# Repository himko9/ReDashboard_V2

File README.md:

# N-in-One Enhanced ReDashboard - Open-Source "EZ Dashboard" Based on the RP2040 MCU

English | [简体中文](./README.zh-CN.md)

<table>
  <tr>
    <td></td>
    <td></td>
  </tr>
  <tr>
    <td></td>
    <td></td>
  </tr>
</table>

### Motherboard Support:

**Supports POST code monitoring through the following headers/interfaces:**

* JDASH1

* JDP1

* JBD1

* Any other UART header using 115200-8N1

**On MSI motherboards, connecting to "JDASH1" provides:**

* Display and logging of POST codes (Port80/81, 8-bit)

* Fan speed display

* System temperature display

* System voltage display

**On MSI motherboards, connecting to "JDP1" provides:**

* Display and logging of POST codes (Port80, 32-bit; Port81-83, 8-bit)

**On other motherboards, connecting to any header that outputs codes over UART 115200-8N1 provides:**

* Display and logging of POST codes (Port80, 8-bit)

**On all motherboards, additional connections to JBAT and JFP1 allow control of:**

* BIOS reset and system power on/off

### Firmware Features:

Code history:\
Supports caching P80 codes in the chip's internal memory.\
The onboard buttons can be used to scroll up and down through the recorded codes.

Code output:\
When connected via USB-C, the device operates as a USB CDC UART device.\
Supports decoded P80 code output.\
A future SDK will support voltage, temperature, and fan-speed logging.

Temperature / voltage / fan-speed sensors:\
Supports custom labels based on motherboard model.\
Supports Celsius / Fahrenheit temperature conversion.

OLED page control:\
Supports disabling unused pages, such as hiding the voltage page.\
Supports automatically returning to the home page after N seconds.\
Supports automatically waking the display when a significant change in temperature, voltage, or fan speed is detected.\
Supports automatically displaying updated POST codes.

OLED burn-in protection features:\
Pixel shifting.\
Automatic dimming.\
Automatic page-title hiding.\
Automatic display shutoff.

### Button Controls:

Short-press both side buttons -> Switch input source (JDASH/UART).\
Hold both side buttons for 3 seconds -> Switch button mode (page navigation mode / power-button mode).\
Hold both side buttons for 5 seconds -> Lock the JDASH/UART input and lock the buttons\
(buttons have no function while locked, Hold again to unlock).\
Hold both side buttons for 10 seconds -> Reset BIOS (NMOS connects JBAT1).

Press either side button 5 times consecutively -> Change page (switch display page).\
On the P80 page, hold either side button -> Scroll up/down through the P80 code history.

### BOM + Manufacturing Notes:
**If you want to reproduce the design directly, please note that the design was imported into JLCPCB/LCEDA from an external source.**\
**I cannot confirm whether Gerber files exported from this project can be used directly for PCB manufacturing.**\
**Please verify the schematic, PCB routing, and copper pours yourself.**\
**Using the Autodesk Eagle design files to generate gerber should be fine**

The reproduction cost is only about RMB 15:\
RMB 6 for a 0.96-inch, 4-pin I2C OLED module.\
RMB 5 for an RP2040 module, from which the RP2040, crystal oscillator, and SPI NOR flash are removed.\
RMB 4 for other capacitors, resistors, LDOs, and miscellaneous components.\
RMB 0 for a free 2-layer PCB (thanks to JLCPCB).

**Note:**\
Reproducing the RP2040 version of ReDashboard is not recommended here.\
A later version will use a PY32 as the main controller, reducing the chip cost significantly to about RMB 0.5, and requiring almost no external components.\
The firmware has already been written and successfully tested. It will be updated when I'm free.\
<br>

### Firmware and Firmware Source Code:
You can use the precompiled `firmware.uf2` file, but it is recommended that you modify the configuration and compile the firmware yourself.
<br>

### License:
Both the hardware and firmware of this project are licensed under the GPL (v3 or later).\
I provide no guarantees regarding the functionality or safety of this project.\
You are free to use, sell, and create products based on this project.

```
/*
 * This file is part of the "ReDashboard_V2" distribution.
 *
 * Copyright (C) 2026 @himko9 <me@himko.dev>
 * Github: https://github.com/himko9/ReDashboard_V2
 *
 * This program is free software: you can redistribute it and/or modify
 * it under the terms of the GNU General Public License as published by
 * the Free Software Foundation, either version 3 of the License, or
 * (at your option) any later version.
 *
 * This program is distributed in the hope that it will be useful,
 * but WITHOUT ANY WARRANTY; without even the implied warranty of
 * MERCHANTABILITY or FITNESS FOR A PARTICULAR PURPOSE.  See the
 * GNU General Public License for more details.
 *
 * You should have received a copy of the GNU General Public License
 * along with this program.  If not, see <https://www.gnu.org/licenses/>.
 */
 ```

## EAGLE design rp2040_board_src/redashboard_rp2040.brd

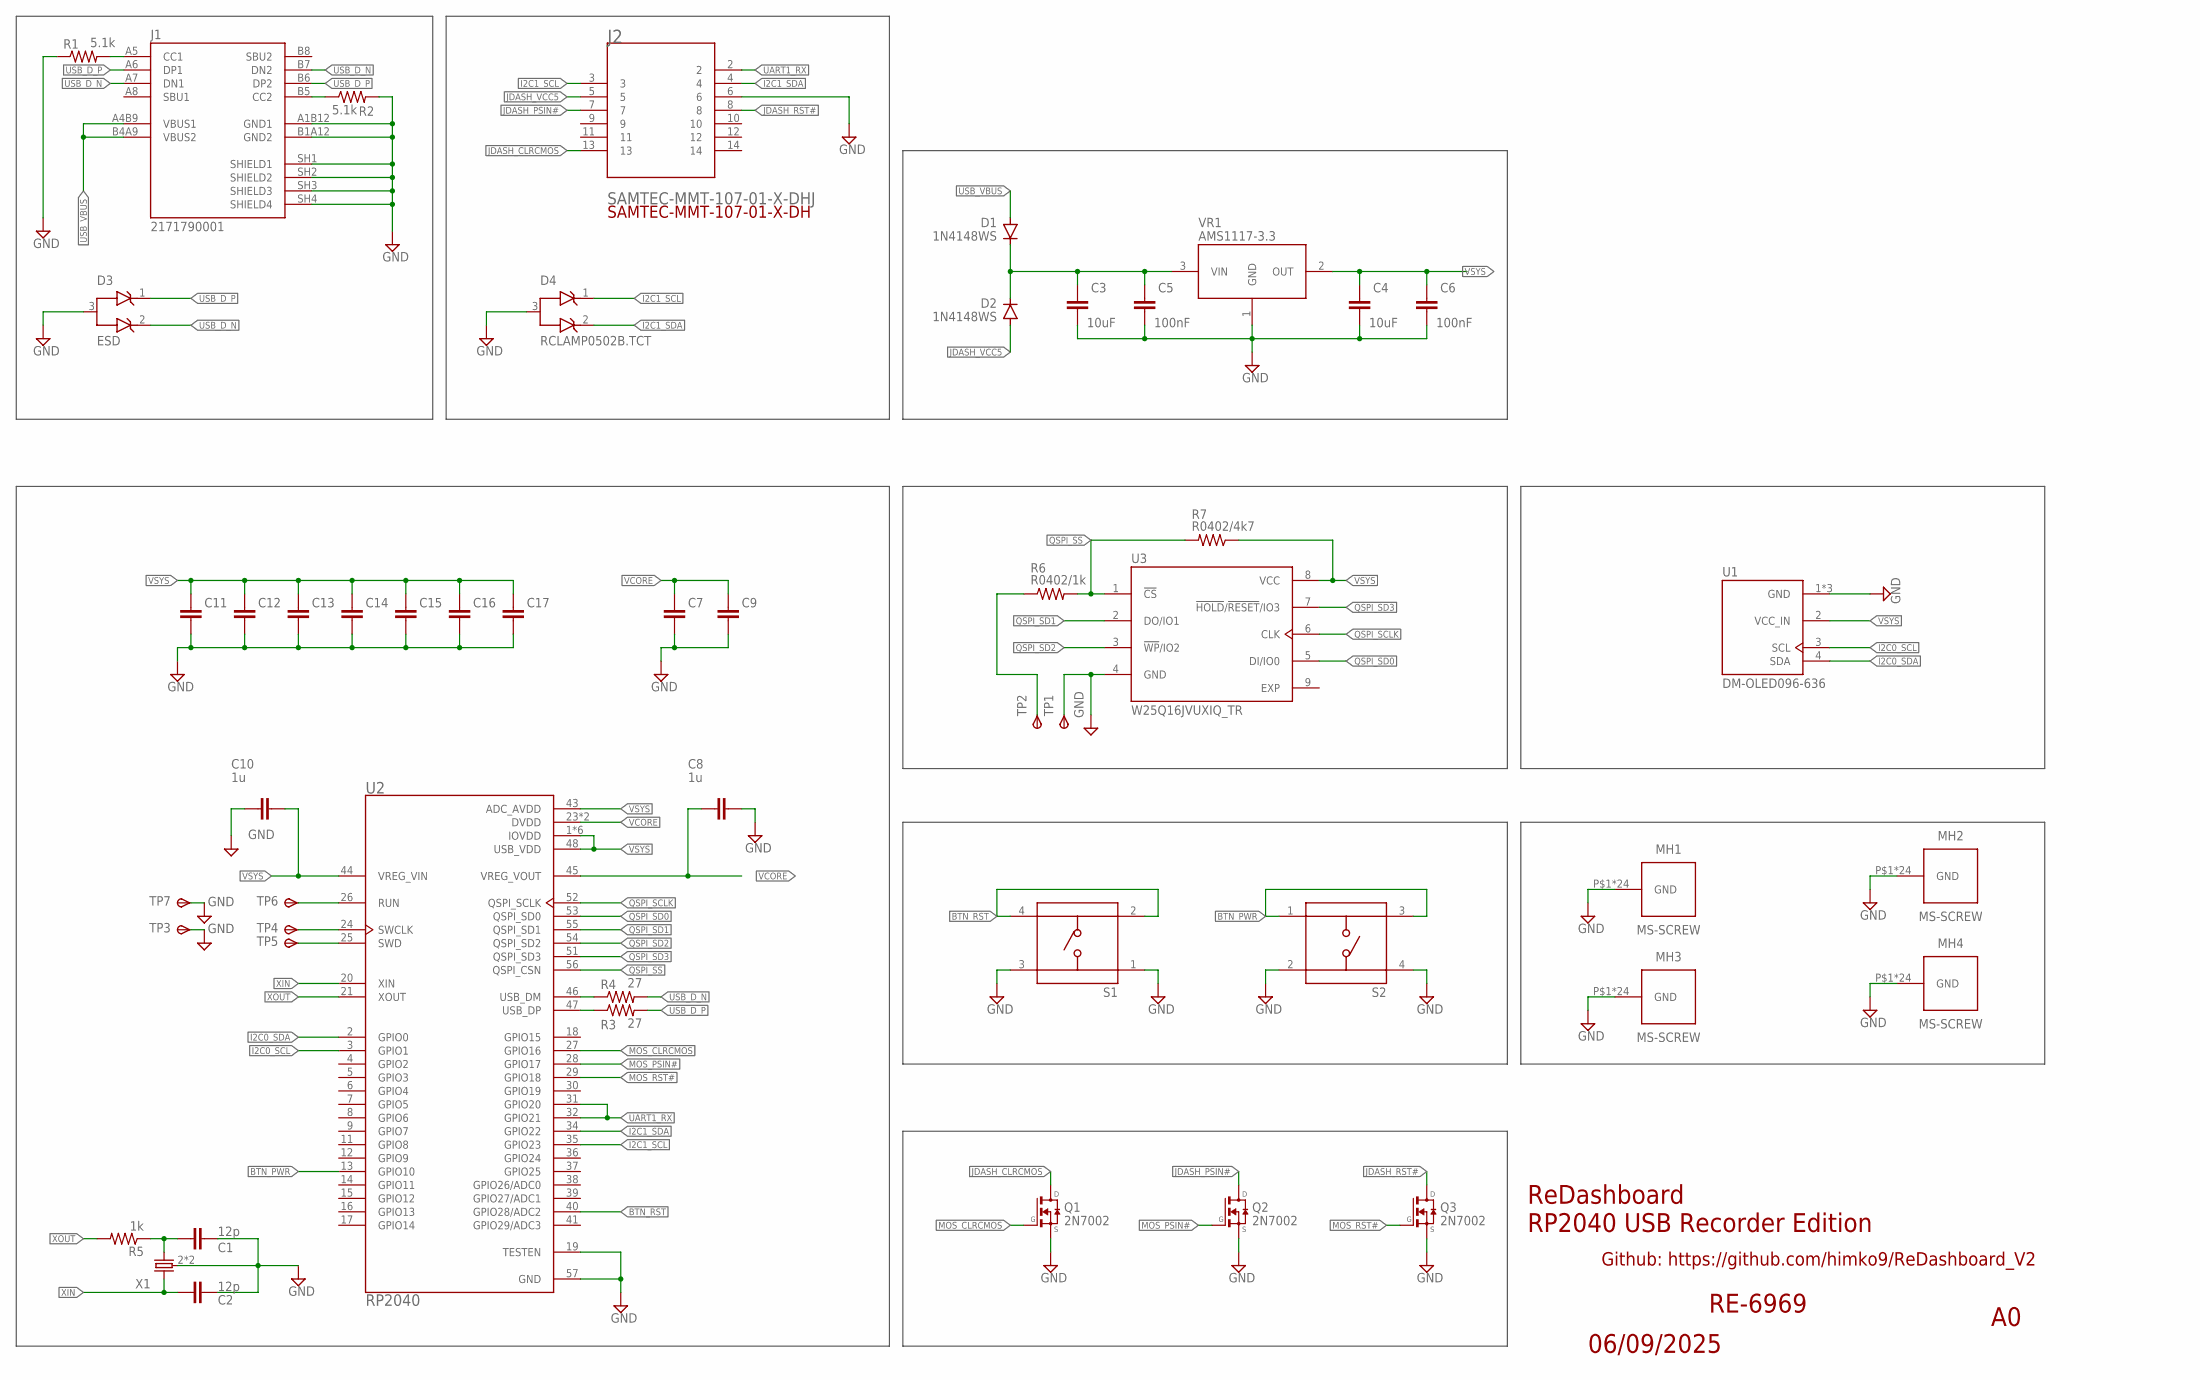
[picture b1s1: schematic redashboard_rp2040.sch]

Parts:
C1, C2: 12p; CAP_0402
C3, C4: 10uF; CAP_0603
C5, C6, C7, C11, C12, C13, C14, C15, C16, C17: 100nF; CAP_0402
C8, C10: 1u; CAP_0402
C9: CC0402CRNPO9BN1R0; CAP_0402
D1, D2: 1N4148WS; SOD-323
D3: ESD; TVS_RCLAMP0502B.TCT
D4: RCLAMP0502B.TCT; TVS_RCLAMP0502B.TCT
J1: 2171790001; MOLEX_2171790001
J2: SAMTEC-MMT-107-01-X-DHJ; SAMTEC-MMT-107-01-X-DH
MH1, MH2, MH3, MH4: MS-SCREW
Q1, Q2, Q3: 2N7002; TRANSISTOR-FET_SOT23
R1, R2: 5.1k; RES_0402
R3, R4: 27; RES_0402
R5: 1k; RES_0402
R6: R0402/1k; RES_0402
R7: R0402/4k7; RES_0402
S1, S2: TS04-66-50-BK-260-SMT; SW_TS04-66-50-BK-260-SMT
TP1, TP3, TP7: TPSTP10SQ; TP10SQ
TP2, TP4, TP5, TP6: TPSTP10R; TP10R
U1: DM-OLED096-636; MODULE_DM-OLED096-636
U2: RP2040; QFN40P700X700X90-57N
U3: W25Q16JVUXIQ_TR; IC_W25Q16JVUXIQ_TR
VR1: AMS1117-3.3; VREG_AZ1117CR2-5.0TRG1
X1: KX-6; 2.5X2.0_KX-6

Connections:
BTN_PWR: S2.1, S2.3, U2.13 (GPIO10)
BTN_RST: S1.2, S1.4, U2.40 (GPIO28/ADC2)
GND: C1.2, C2.2, C3.2, C4.2, C5.2, C6.2, C7.2, C8.2, C9.2, C10.1, C11.2, C12.2, C13.2, C14.2, C15.2, C16.2, C17.2, D3.3 (A), D4.3 (A), J1.A1B12 (GND1), J1.B1A12 (GND2), J1.SH1 (SHIELD1), J1.SH2 (SHIELD2), J1.SH3 (SHIELD3), J1.SH4 (SHIELD4), J2.6, MH1.P$1, MH1.P$2, MH1.P$3, MH1.P$4, MH1.P$5, MH1.P$6, MH1.P$7, MH1.P$8, MH1.P$9, MH1.P$10, MH1.P$11, MH1.P$12, MH1.P$13, MH1.P$14, MH1.P$15, MH1.P$16, MH1.P$17, MH1.P$18, MH1.P$19, MH1.P$20, MH1.P$21, MH1.P$22, MH1.P$23, MH1.P$24, MH2.P$1, MH2.P$2, MH2.P$3, MH2.P$4, MH2.P$5, MH2.P$6, MH2.P$7, MH2.P$8, MH2.P$9, MH2.P$10, MH2.P$11, MH2.P$12, MH2.P$13, MH2.P$14, MH2.P$15, MH2.P$16, MH2.P$17, MH2.P$18, MH2.P$19, MH2.P$20, MH2.P$21, MH2.P$22, MH2.P$23, MH2.P$24, MH3.P$1, MH3.P$2, MH3.P$3, MH3.P$4, MH3.P$5, MH3.P$6, MH3.P$7, MH3.P$8, MH3.P$9, MH3.P$10, MH3.P$11, MH3.P$12, MH3.P$13, MH3.P$14, MH3.P$15, MH3.P$16, MH3.P$17, MH3.P$18, MH3.P$19, MH3.P$20, MH3.P$21, MH3.P$22, MH3.P$23, MH3.P$24, MH4.P$1, MH4.P$2, MH4.P$3, MH4.P$4, MH4.P$5, MH4.P$6, MH4.P$7, MH4.P$8, MH4.P$9, MH4.P$10, MH4.P$11, MH4.P$12, MH4.P$13, MH4.P$14, MH4.P$15, MH4.P$16, MH4.P$17, MH4.P$18, MH4.P$19, MH4.P$20, MH4.P$21, MH4.P$22, MH4.P$23, MH4.P$24, Q1.2 (S), Q2.2 (S), Q3.2 (S), R1.1, R2.2, S1.1, S1.3, S2.2, S2.4, TP1.TP, TP3.TP, TP7.TP, U1.1 (GND), U1.S3 (GND), U1.S4 (GND), U2.19 (TESTEN), U2.57 (GND), U3.4 (GND), VR1.1 (GND), X1.2 (3), X1.4 (3)
I2C0_SCL: U1.3 (SCL), U2.3 (GPIO1)
I2C0_SDA: U1.4 (SDA), U2.2 (GPIO0)
I2C1_SCL: D4.1 (K1), J2.3, U2.35 (GPIO23)
I2C1_SDA: D4.2 (K2), J2.4, U2.34 (GPIO22)
JDASH_CLRCMOS: J2.13, Q1.3 (D)
JDASH_PSIN#: J2.7, Q2.3 (D)
JDASH_RST#: J2.8, Q3.3 (D)
JDASH_VCC5: D2.A, J2.5
MOS_CLRCMOS: Q1.1 (G), U2.27 (GPIO16)
MOS_PSIN#: Q2.1 (G), U2.28 (GPIO17)
MOS_RST#: Q3.1 (G), U2.29 (GPIO18)
unnamed: R6.1, TP2.TP
unnamed: C3.1, C5.1, D1.C, D2.C, VR1.3 (VIN)
unnamed: J1.B5 (CC2), R2.1
unnamed: C1.1, R5.1, X1.3 (2)
unnamed: J1.A5 (CC1), R1.2
unnamed: TP6.TP, U2.26 (RUN)
unnamed: TP4.TP, U2.24 (SWCLK)
unnamed: TP5.TP, U2.25 (SWD)
QSPI_SCLK: U2.52 (QSPI_SCLK), U3.6 (CLK)
QSPI_SD0: U2.53 (QSPI_SD0), U3.5 (DI/IO0)
QSPI_SD1: U2.55 (QSPI_SD1), U3.2 (DO/IO1)
QSPI_SD2: U2.54 (QSPI_SD2), U3.3 (!WP!/IO2)
QSPI_SD3: U2.51 (QSPI_SD3), U3.7 (!HOLD!/!RESET!/IO3)
QSPI_SS: R6.2, R7.2, U2.56 (QSPI_CSN), U3.1 (!CS)
UART1_RX: J2.2, U2.31 (GPIO20), U2.32 (GPIO21)
USB_D_N: D3.2 (K2), J1.A7 (DN1), J1.B7 (DN2), R4.2
USB_D_P: D3.1 (K1), J1.A6 (DP1), J1.B6 (DP2), R3.2
USB_D_R_N: R4.1, U2.46 (USB_DM)
USB_D_R_P: R3.1, U2.47 (USB_DP)
USB_VBUS: D1.A, J1.A4B9 (VBUS1), J1.B4A9 (VBUS2)
VCORE: C7.1, C8.1, C9.1, U2.23 (DVDD), U2.45 (VREG_VOUT), U2.50 (DVDD)
VSYS: C4.1, C6.1, C10.2, C11.1, C12.1, C13.1, C14.1, C15.1, C16.1, C17.1, R7.1, U1.2 (VCC_IN), U2.1 (IOVDD), U2.10 (IOVDD), U2.22 (IOVDD), U2.33 (IOVDD), U2.42 (IOVDD), U2.43 (ADC_AVDD), U2.44 (VREG_VIN), U2.48 (USB_VDD), U2.49 (IOVDD), U3.8 (VCC), VR1.2 (OUT)
XIN: C2.1, U2.20 (XIN), X1.1
XOUT: R5.2, U2.21 (XOUT)

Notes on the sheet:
RE-6969
ReDashboard RP2040 USB Recorder Edition
06/09/2025
Github: https://github.com/himko9/ReDashboard_V2

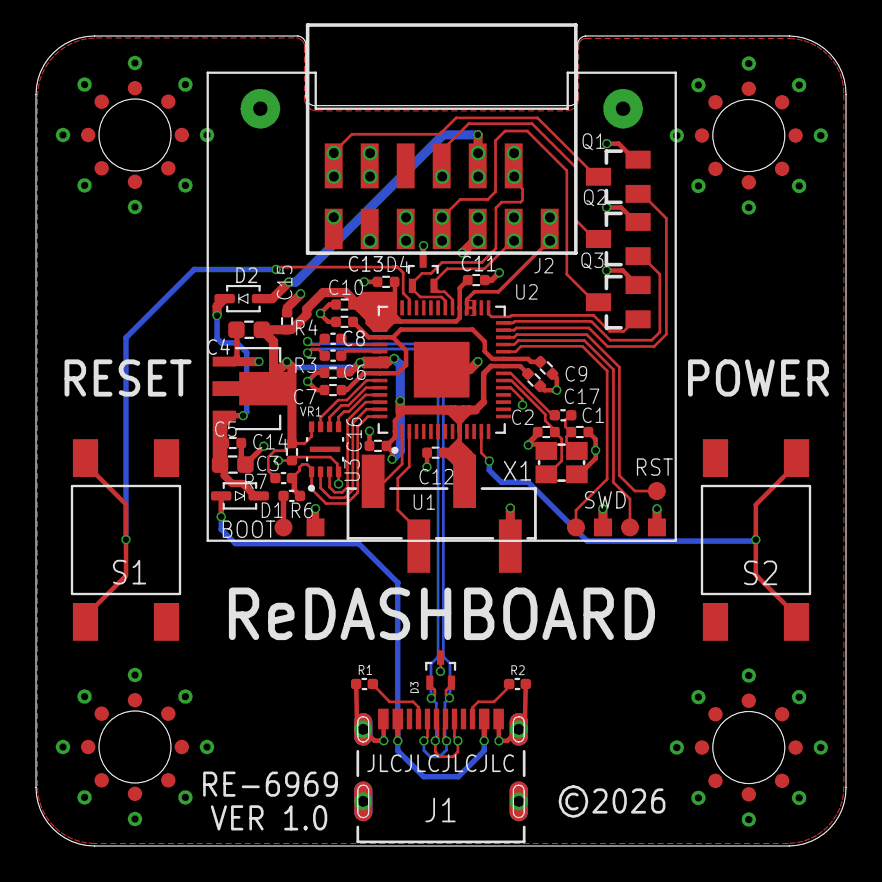
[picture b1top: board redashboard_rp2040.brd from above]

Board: 2 copper layers, 45.0 x 45.0 mm, 51 parts (0 on the bottom side), 38 nets.

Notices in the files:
rp2040_board_src/redashboard_rp2040.brd:
©2026
